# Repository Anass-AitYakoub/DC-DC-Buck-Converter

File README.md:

# DC-DC Buck Converter | 12V to 5V, 2A

**Custom PCB Design & Power Electronics Simulation**

A personal electrical engineering project focused on designing and analyzing a 12V-to-5V DC-DC buck converter capable of supplying a target output current of 2A.

The project combines PCB design in KiCad, theoretical power electronics calculations, and MATLAB/Simulink simulations.

**Project Status:** PCB designed; hardware assembly and testing pending.

## Project Objectives

- Design a custom two-layer PCB using KiCad.
- Implement an adjustable LM2596-based buck converter.
- Convert a nominal 12V DC input to a regulated 5V output.
- Target an output current of up to 2A.
- Model switching behavior using MATLAB and Simscape Electrical.
- Analyze startup response, inductor current, voltage ripple, load regulation, and efficiency.
- Compare simulation results against physical measurements after PCB assembly.

## Technical Specifications

| Parameter | Value |
|---|---|
| Input Voltage | 12V DC nominal |
| Target Output Voltage | 5V DC |
| Target Output Current | 2A |
| Target Output Power | 10W |
| Regulator IC | LM2596T-ADJ |
| Switching Frequency | 150 kHz |
| Inductor | 68 µH |
| Output Capacitor | 470 µF |
| PCB | Custom 2-layer PCB |

## Technologies Used

- **KiCad:** Circuit schematic, PCB layout and Gerber generation
- **MATLAB:** Numerical calculations, signal analysis and visualization
- **Simulink / Simscape Electrical:** Switching circuit simulation
- **LTspice:** Circuit simulation tool for subsequent validation

## MATLAB/Simulink Simulation

A simplified open-loop buck converter was modeled using a fixed 45% PWM duty cycle at 150 kHz.

The model includes an inductor series resistance of 0.067 Ohm and an assumed output capacitor ESR of 0.05 Ohm.

The open-loop model is not an exact representation of the LM2596 internal feedback controller.

### Startup Transient Response

The fixed-PWM model exhibits transient overshoot and damped oscillations before approaching steady-state operation.

### Inductor Current Ripple

The simulated inductor current is approximately 2A with a peak-to-peak ripple of about 0.303A under the nominal load condition.

### Output Voltage Ripple

The simulated steady-state output voltage ripple is approximately 14.96mV peak-to-peak with the assumed capacitor ESR.

### Load Regulation

The fixed-duty-cycle model shows a gradual decrease in output voltage as load current increases.

### Soft-Start Investigation

A separate simulation explored a 5ms duty-cycle ramp to reduce startup overshoot.

At approximately 1.5A output current, the simulated startup peak decreased from about 7.489V with fixed PWM to 5.150V with the ramped-duty-cycle strategy.

**Note:** The soft-start investigation is simulation-only and does not represent an implemented soft-start circuit on the LM2596 PCB.

## Efficiency Analysis

Simulated performance across four resistive load conditions:

| Output Current | Output Voltage | Simulated Efficiency |
|---|---|---|
| 0.509 A | 5.086 V | 95.47% |
| 1.010 A | 5.047 V | 94.37% |
| 1.503 A | 5.009 V | 93.54% |
| 1.989 A | 4.972 V | 92.78% |

Input and output powers were calculated using time-weighted integration in MATLAB.

A maximum simulation step of 0.1 microseconds was used to improve the accuracy of switching-waveform analysis.

These values represent the simplified Simscape model, not measured efficiency of the physical LM2596 converter.

## Repository Structure

```text
DC_DC_Buck_Converter/
├── README.md
├── MATLAB_Simulink/
│   ├── Models/
│   ├── Scripts/
│   ├── Results/
│   │   ├── Figures/
│   │   └── Data/
│   └── Documentation/
│       └── DC_DC_Buck_Converter_Simulation_Report.docx
└── KiCad design files
```

## Technical Report

[View the Design and Simulation Report](MATLAB_Simulink/Documentation/DC_DC_Buck_Converter_Simulation_Report.docx)

The report documents the simulation methodology, results, limitations and planned hardware validation.

## Hardware Validation Plan

After PCB manufacturing and assembly, the following tests are planned:

1. Verify PCB assembly and electrical continuity.
2. Perform initial power-up using a current-limited 12V supply.
3. Measure the unloaded output voltage.
4. Test output regulation at approximately 0.5A, 1A, 1.5A and 2A.
5. Measure input and output current and voltage.
6. Calculate experimental conversion efficiency.
7. Compare experimental results with MATLAB/Simulink predictions.
8. Investigate component heating and output ripple where suitable measurement equipment is available.

## Project Status

- [x] Circuit design and component selection
- [x] Custom PCB layout in KiCad
- [x] PCB design-rule check
- [x] MATLAB theoretical calculations
- [x] Simulink switching circuit model
- [x] Startup and ripple analysis
- [x] Load regulation analysis
- [x] Soft-start simulation investigation
- [x] Simulated efficiency analysis
- [x] Simulation report
- [ ] PCB assembly
- [ ] Hardware performance measurements
- [ ] Simulation-to-hardware comparison

## Author

Electrical Engineering Student  
Concordia University, Montreal, Canada

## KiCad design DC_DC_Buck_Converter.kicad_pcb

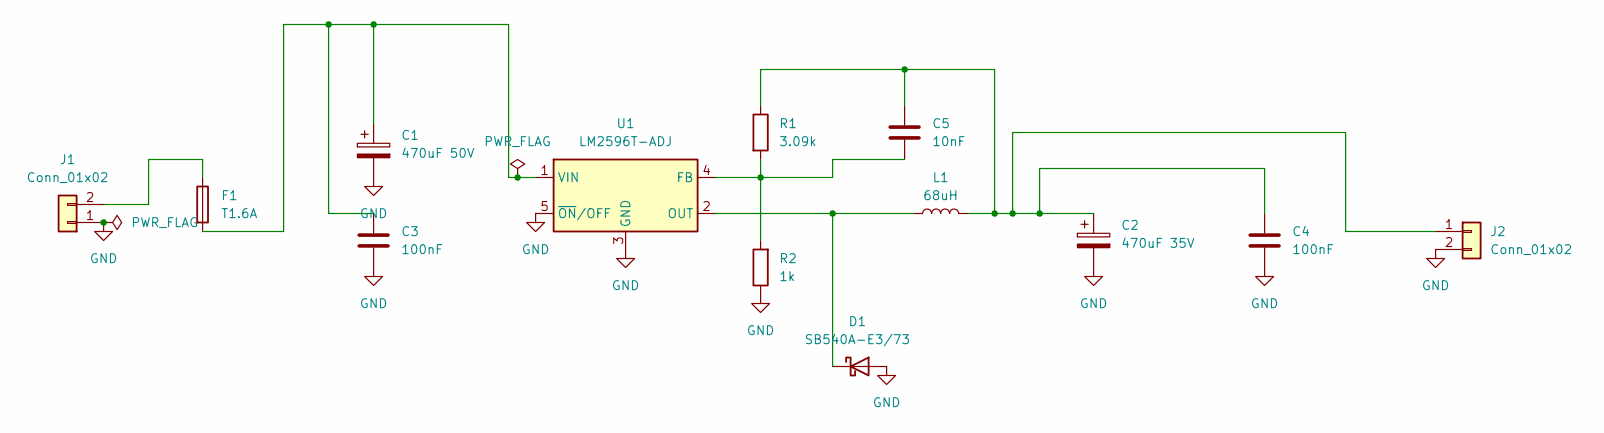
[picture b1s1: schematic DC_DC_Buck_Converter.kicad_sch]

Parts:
C1: 470uF 50V; CP_Radial_D12.5mm_P5.00mm
C2: 470uF 35V; CP_Radial_D10.0mm_P5.00mm
C3, C4: 100nF; C_Rect_L4.0mm_W2.5mm_P2.50mm
C5: 10nF; C_Rect_L4.0mm_W2.5mm_P2.50mm
D1: SB540A-E3/73; D_DO-201AD_P15.24mm_Horizontal
F1: T1.6A; Fuseholder_Wurth_696309001002
J1, J2: Conn_01x02; TerminalBlock_SameSky_TB004-508-02BE; MPN TB004-508-02BE
L1: 68uH; L_Toroid_Horizontal_D21.8mm_P19.10mm_Bourns_2100
R1: 3.09k; R_Axial_DIN0207_L6.3mm_D2.5mm_P7.62mm_Horizontal
R2: 1k; R_Axial_DIN0207_L6.3mm_D2.5mm_P7.62mm_Horizontal
U1: LM2596T-ADJ; TO-220-5_P3.4x3.7mm_StaggerOdd_Lead3.8mm_Vertical

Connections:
GND: C1.2, C2.2, C3.2, C4.2, D1.2 (A), J1.1, J2.2, R2.1, U1.3 (GND), U1.5 (~ON/OFF)
unnamed: D1.1 (K), L1.1, U1.2 (OUT)
unnamed: F1.1, J1.2
unnamed: C2.1, C4.1, C5.1, J2.1, L1.2, R1.1
unnamed: C5.2, R1.2, R2.2, U1.4 (FB)
unnamed: C1.1, C3.1, F1.2, U1.1 (VIN)

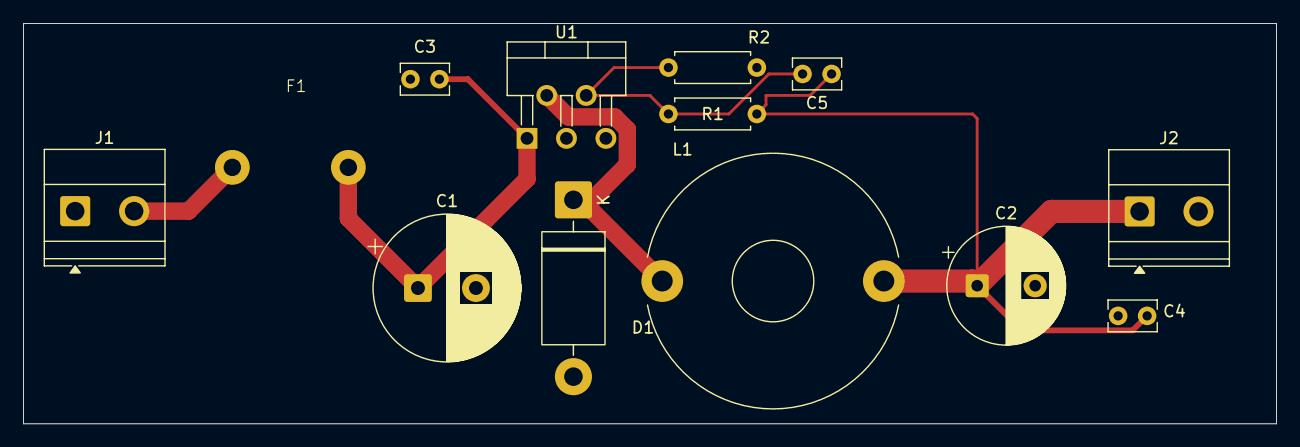
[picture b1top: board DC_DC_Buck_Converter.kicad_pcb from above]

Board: 2 copper layers, 108.0 x 34.5 mm, 13 parts (0 on the bottom side), 6 nets.
